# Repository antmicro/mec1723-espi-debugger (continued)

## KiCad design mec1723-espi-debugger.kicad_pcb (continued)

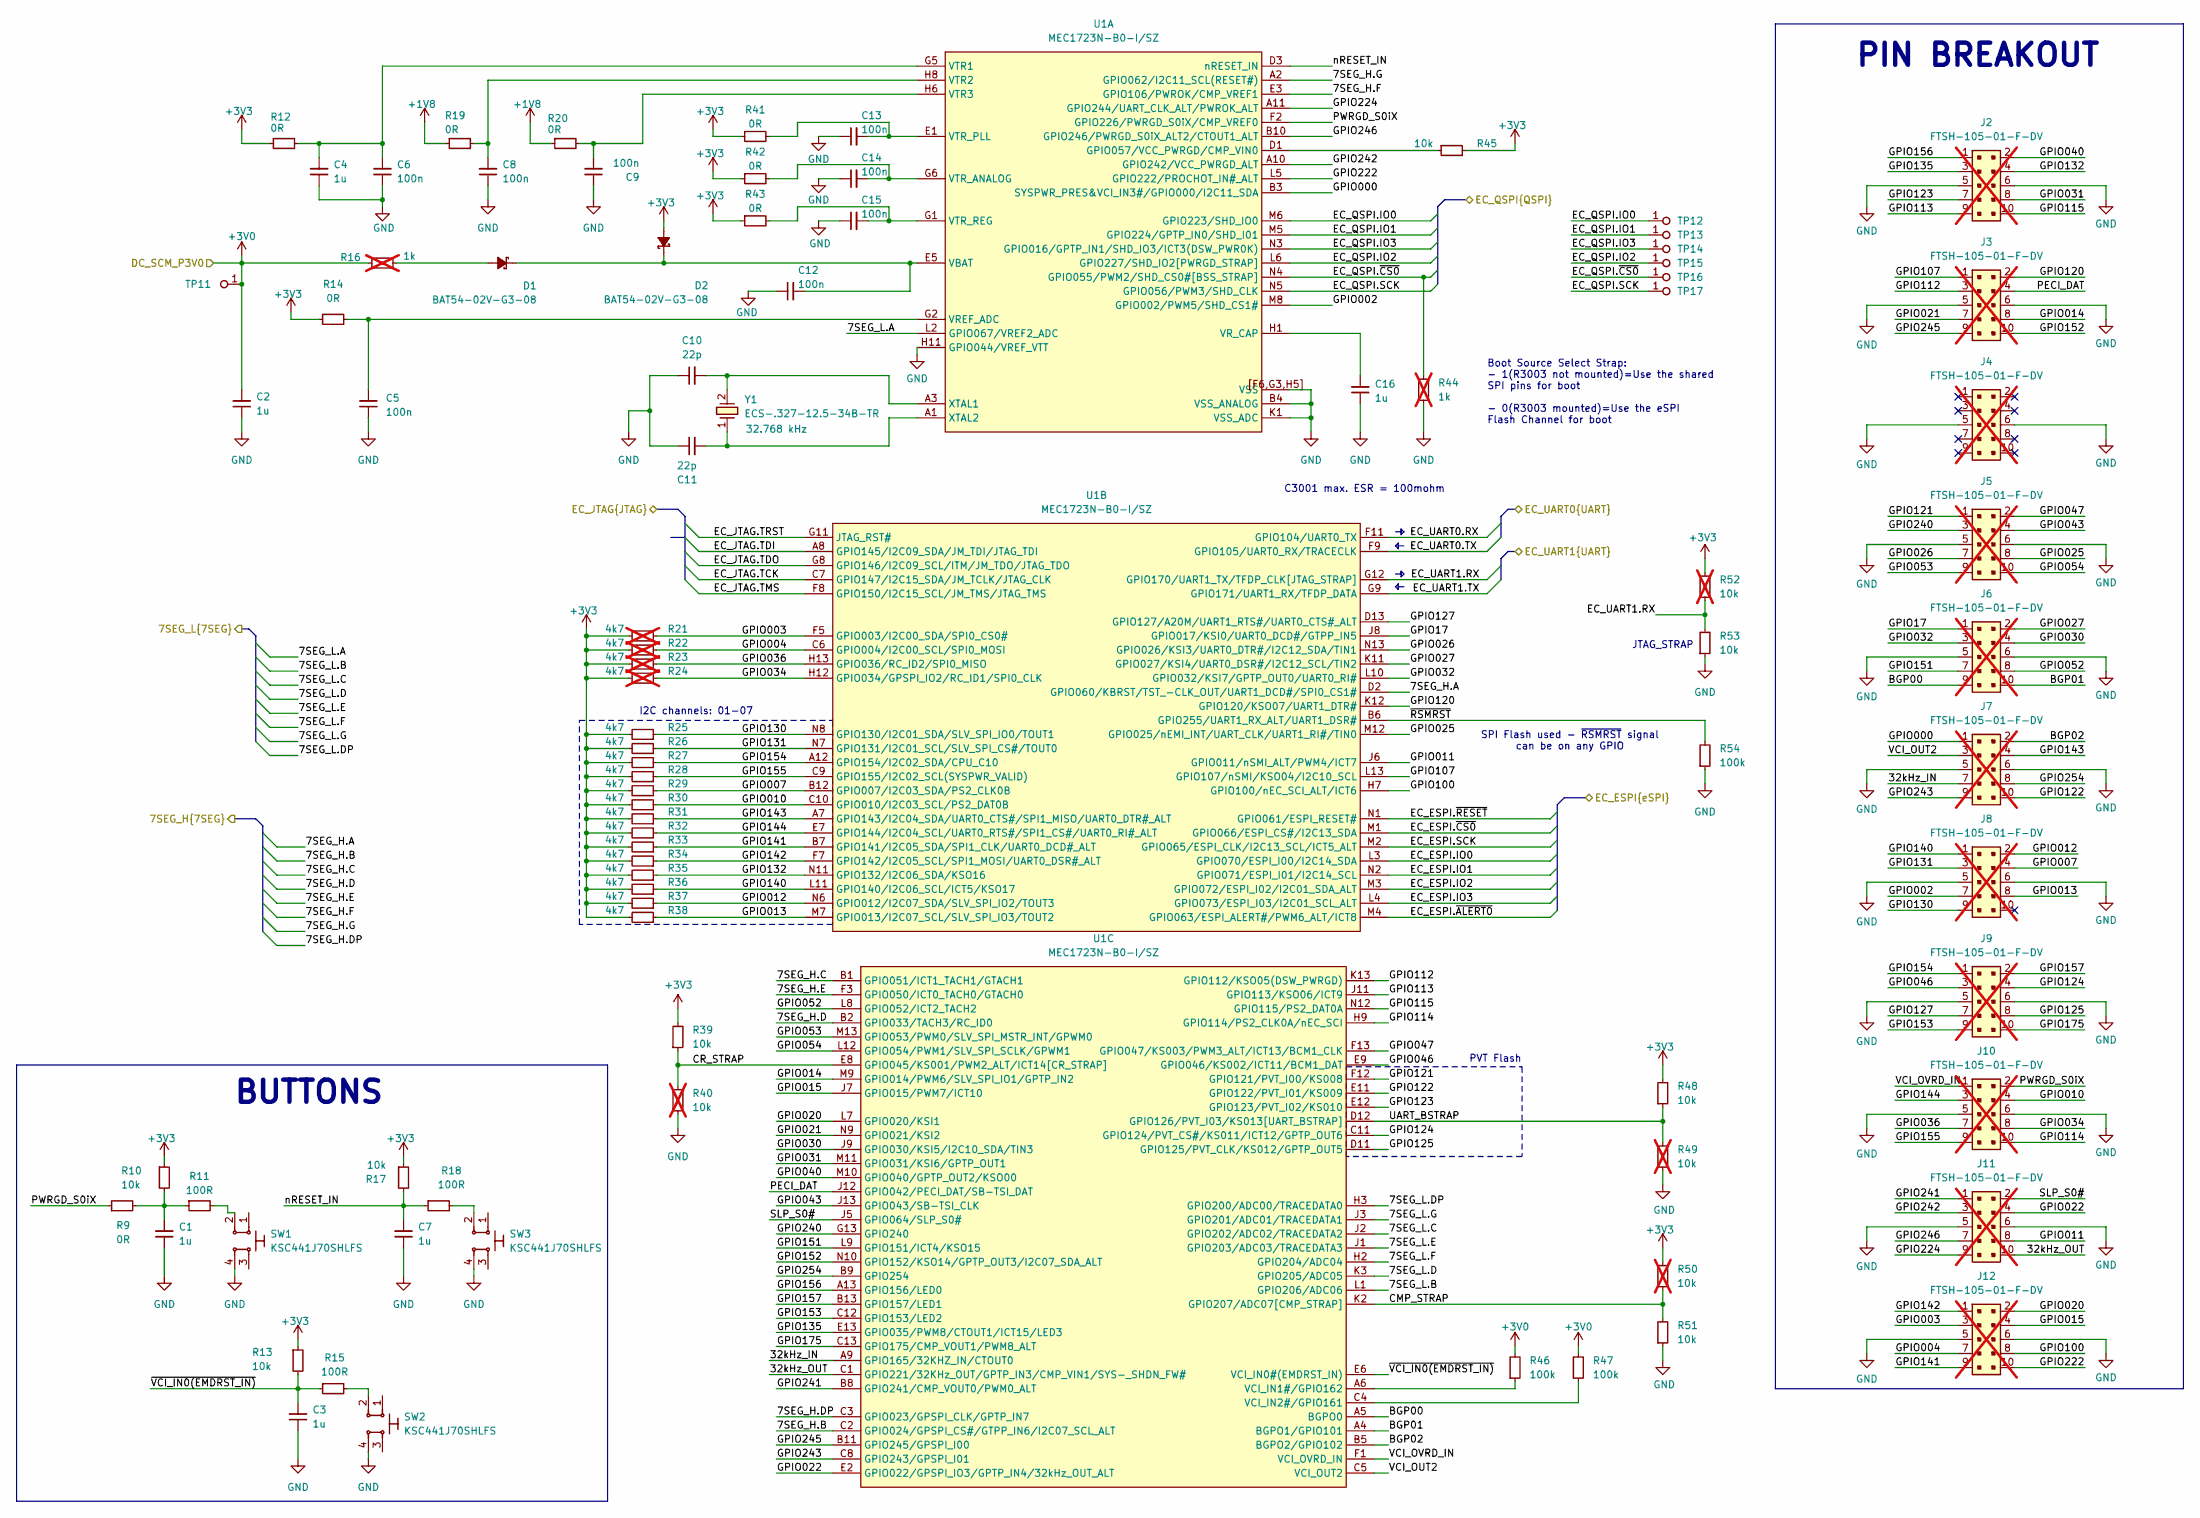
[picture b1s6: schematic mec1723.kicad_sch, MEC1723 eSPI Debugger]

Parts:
C1, C3, C7: C_1u_6.3V_X6S_0402; C_0402_1005Metric; Voltage 6.3V; MPN GRT155C80J105KE01D
C2, C4, C16: C_1u_0603; C_0603_1608Metric; MPN 0603YD105KAT2A
C5, C9, C12, C13, C14, C15: C_100n_0402; C_0402_1005Metric; Voltage 50V; MPN GRM155R61H104KE14D
C6, C8: C_100n_16V_X7R_0402; C_0402_1005Metric; Voltage 16V; MPN C0402C104J4RAC7411
C10, C11: C_22p_0402; C_0402_1005Metric; MPN CC0402JRNPO9BN220
D1, D2: BAT54-02V-G3-08; SOD-523; MPN BAT54-02V-G3-08
J2, J3, J4, J5, J6, J7, J8, J9, J10, J11, J12: PinHeader_2x5_P1.27mm_SMD; MPN FTSH-105-01-F-DV; not fitted
R9, R12, R14, R19, R20, R41, R42, R43: R_0R_0402; R_0402_1005Metric; MPN ERJ2GE0R00X
R10, R13, R17, R39, R45, R48, R51, R53: R_10k_0402; R_0402_1005Metric; Tolerance 1%; MPN CR0402-FX-1002GLF
R11, R15, R18: R_100R_0402; R_0402_1005Metric; Tolerance 1%; MPN CR0402-FX-1000GLF
R16, R44: R_1k_0402; R_0402_1005Metric; Tolerance 1%; MPN CR0402-FX-1001GLF; not fitted
R21, R22, R23, R24: R_4k7_0402; R_0402_1005Metric; Tolerance 1%; MPN CR0402-FX-4701GLF; not fitted
R25, R26, R27, R28, R29, R30, R31, R32, R33, R34, R35, R36, R37, R38: R_4k7_0402; R_0402_1005Metric; Tolerance 1%; MPN CR0402-FX-4701GLF
R40, R49, R50, R52: R_10k_0402; R_0402_1005Metric; Tolerance 1%; MPN CR0402-FX-1002GLF; not fitted
R46, R47, R54: R_100k_0402; R_0402_1005Metric; Tolerance 1%; MPN CR0402-FX-1003GLF
SW1, SW2, SW3: SW_KSC441J70SHLFS_SMD; MPN KSC441J70SHLFS
TP11, TP12, TP13, TP14, TP15, TP16, TP17: TP_1mm_SMD; TP_SMD_1mm
U1: MEC1723N-B0-I/SZ; BGA-169-144_9x9mm_Layout13x13_P0.7mm; MPN MEC1723N-B0-I/SZ
Y1: Resonator_32.768kHz_ECX-31B; Resonator_SMD_ECS_ECX-31B_3.2x1.5x0.9mm; MPN ECS-.327-12.5-34B-TR

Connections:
+1V8: R19.1, R20.1; also elsewhere on the board
+3V0: C2.2, R16.1, R46.2, R47.2, TP11.1 (1_1); also elsewhere on the board
+3V3: D2.2 (A), R10.1, R12.1, R13.1, R14.1, R17.1, R21.2, R22.2, R23.2, R24.2, R25.2, R26.2, R27.2, R28.2, R29.2, R30.2, R31.2, R32.2, R33.2, R34.2, R35.2, R36.2, R37.2, R38.2, R39.2, R41.1, R42.1, R43.1, R45.2, R48.2, R50.2, R52.2; also elsewhere on the board
/Connectors/EC_JTAG.TCK: U1.C7 (GPIO147/I2C15_SDA/JM_TCLK/JTAG_CLK); also elsewhere on the board
/Connectors/EC_JTAG.TDI: U1.A8 (GPIO145/I2C09_SDA/JM_TDI/JTAG_TDI); also elsewhere on the board
/Connectors/EC_JTAG.TDO: U1.G8 (GPIO146/I2C09_SCL/ITM/JM_TDO/JTAG_TDO); also elsewhere on the board
/Connectors/EC_JTAG.TMS: U1.F8 (GPIO150/I2C15_SCL/JM_TMS/JTAG_TMS); also elsewhere on the board
/Connectors/EC_JTAG.TRST: U1.G11 (JTAG_RST#); also elsewhere on the board
/Connectors/EC_UART0.RX: U1.F11 (GPIO104/UART0_TX); also elsewhere on the board
/Connectors/EC_UART0.TX: U1.F9 (GPIO105/UART0_RX/TRACECLK); also elsewhere on the board
/Connectors/EC_UART1.RX: R52.1, R53.2, U1.G12 (GPIO170/UART1_TX/TFDP_CLK[JTAG_STRAP]); also elsewhere on the board
/Connectors/EC_UART1.TX: U1.G9 (GPIO171/UART1_RX/TFDP_DATA); also elsewhere on the board
/DC-SCM Interposer connector/EC_ESPI.IO0: U1.L3 (GPIO070/ESPI_I00/I2C14_SDA); also elsewhere on the board
/DC-SCM Interposer connector/EC_ESPI.IO1: U1.N2 (GPIO071/ESPI_I01/I2C14_SCL); also elsewhere on the board
/DC-SCM Interposer connector/EC_ESPI.IO2: U1.M3 (GPIO072/ESPI_I02/I2C01_SDA_ALT); also elsewhere on the board
/DC-SCM Interposer connector/EC_ESPI.IO3: U1.L4 (GPIO073/ESPI_I03/I2C01_SCL_ALT); also elsewhere on the board
/DC-SCM Interposer connector/EC_ESPI.SCK: U1.M2 (GPIO065/ESPI_CLK/I2C13_SCL/ICT5_ALT); also elsewhere on the board
/DC-SCM Interposer connector/EC_ESPI.~ALERT0: U1.M4 (GPIO063/ESPI_ALERT#/PWM6_ALT/ICT8); also elsewhere on the board
/DC-SCM Interposer connector/EC_ESPI.~CS0: U1.M1 (GPIO066/ESPI_CS#/I2C13_SDA); also elsewhere on the board
/DC-SCM Interposer connector/EC_ESPI.~RESET: U1.N1 (GPIO061/ESPI_RESET#); also elsewhere on the board
/Flash/EC_QSPI.IO0: TP12.1 (1_1), U1.M6 (GPIO223/SHD_IO0); also elsewhere on the board
/Flash/EC_QSPI.IO1: TP13.1 (1_1), U1.M5 (GPIO224/GPTP_IN0/SHD_I01); also elsewhere on the board
/Flash/EC_QSPI.IO2: TP15.1 (1_1), U1.L6 (GPIO227/SHD_IO2[PWRGD_STRAP]); also elsewhere on the board
/Flash/EC_QSPI.IO3: TP14.1 (1_1), U1.N3 (GPIO016/GPTP_IN1/SHD_IO3/ICT3(DSW_PWR0K)); also elsewhere on the board
/Flash/EC_QSPI.SCK: TP17.1 (1_1), U1.N5 (GPIO056/PWM3/SHD_CLK); also elsewhere on the board
/Flash/EC_QSPI.~CS0: R44.2, TP16.1 (1_1), U1.N4 (GPIO055/PWM2/SHD_CS0#[BSS_STRAP]); also elsewhere on the board
/MEC1723/7SEG_H.A: U1.D2 (GPIO060/KBRST/TST_-CLK_OUT/UART1_DCD#/S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); also elsewhere on the board
/MEC1723/7SEG_H.B: U1.C2 (GPIO024/GPSPI_CS#/GTPP_IN6/I2C07_SCL_ALT); also elsewhere on the board
/MEC1723/7SEG_H.C: U1.B1 (GPIO051/ICT1_TACH1/GTACH1); also elsewhere on the board
/MEC1723/7SEG_H.D: U1.B2 (GPIO033/TACH3/RC_ID0); also elsewhere on the board
/MEC1723/7SEG_H.DP: U1.C3 (GPIO023/GPSPI_CLK/GPTP_IN7); also elsewhere on the board
/MEC1723/7SEG_H.E: U1.F3 (GPIO050/ICT0_TACH0/GTACH0); also elsewhere on the board
/MEC1723/7SEG_H.F: U1.E3 (GPIO106/PWROK/CMP_VREF1); also elsewhere on the board
/MEC1723/7SEG_H.G: U1.A2 (GPIO062/I2C11_SCL(RESET#)); also elsewhere on the board
/MEC1723/7SEG_L.A: U1.L2 (GPIO067/VREF2_ADC); also elsewhere on the board
/MEC1723/7SEG_L.B: U1.L1 (GPIO206/ADC06); also elsewhere on the board
/MEC1723/7SEG_L.C: U1.J2 (GPIO202/ADC02/TRACEDATA2); also elsewhere on the board
/MEC1723/7SEG_L.D: U1.K3 (GPIO205/ADC05); also elsewhere on the board
/MEC1723/7SEG_L.DP: U1.H3 (GPIO200/ADC00/TRACEDATA0); also elsewhere on the board
/MEC1723/7SEG_L.E: U1.J1 (GPIO203/ADC03/TRACEDATA3); also elsewhere on the board
/MEC1723/7SEG_L.F: U1.H2 (GPIO204/ADC04); also elsewhere on the board
/MEC1723/7SEG_L.G: U1.J3 (GPIO201/ADC01/TRACEDATA1); also elsewhere on the board
/MEC1723/32kHz_IN: J7.7, U1.A9 (GPIO165/32KHZ_IN/CTOUT0)
/MEC1723/32kHz_OUT: J11.10, U1.C1 (GPIO221/32KHz_OUT/GPTP_IN3/CMP_VIN1/SYS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)
/MEC1723/BGP00: J6.9, U1.A5 (BGPO0)
/MEC1723/BGP01: J6.10, U1.A4 (BGPO1/GPIO101)
/MEC1723/BGP02: J7.2, U1.B5 (BGPO2/GPIO102)
/MEC1723/CMP_STRAP: R50.1, R51.2, U1.K2 (GPIO207/ADC07[CMP_STRAP])
/MEC1723/CR_STRAP: R39.1, R40.2, U1.E8 (GPIO045/KS001/PWM2_ALT/ICT14[CR_STRAP])
/MEC1723/GPIO000: J7.1, U1.B3 (SYSPWR_PRES&VCI_IN3#/GPIO000/I2C11_SDA)
/MEC1723/GPIO002: J8.7, U1.M8 (GPIO002/PWM5/SHD_CS1#)
/MEC1723/GPIO003: J12.3, R21.1, U1.F5 (GPIO003/I2C00_SDA/SPI0_CS0#)
/MEC1723/GPIO004: J12.7, R22.1, U1.C6 (GPIO004/I2C00_SCL/SPI0_MOSI)
/MEC1723/GPIO007: J8.4, R29.1, U1.B12 (GPIO007/I2C03_SDA/PS2_CLK0B)
/MEC1723/GPIO010: J10.4, R30.1, U1.C10 (GPIO010/I2C03_SCL/PS2_DAT0B)
/MEC1723/GPIO011: J11.8, U1.J6 (GPIO011/nSMI_ALT/PWM4/ICT7)
/MEC1723/GPIO012: J8.2, R37.1, U1.N6 (GPIO012/I2C07_SDA/SLV_SPI_IO2/TOUT3)
/MEC1723/GPIO013: J8.8, R38.1, U1.M7 (GPIO013/I2C07_SCL/SLV_SPI_IO3/TOUT2)
/MEC1723/GPIO014: J3.8, U1.M9 (GPIO014/PWM6/SLV_SPI_IO1/GPTP_IN2)
/MEC1723/GPIO015: J12.4, U1.J7 (GPIO015/PWM7/ICT10)
/MEC1723/GPIO17: J6.1, U1.J8 (GPIO017/KSI0/UART0_DCD#/GTPP_IN5)
/MEC1723/GPIO020: J12.2, U1.L7 (GPIO020/KSI1)
/MEC1723/GPIO021: J3.7, U1.N9 (GPIO021/KSI2)
/MEC1723/GPIO022: J11.4, U1.E2 (GPIO022/GPSPI_IO3/GPTP_IN4/32kHz_OUT_ALT)
/MEC1723/GPIO025: J5.8, U1.M12 (GPIO025/nEMI_INT/UART_CLK/UART1_RI#/TIN0)
/MEC1723/GPIO026: J5.7, U1.N13 (GPIO026/KSI3/UART0_DTR#/I2C12_SDA/TIN1)
/MEC1723/GPIO027: J6.2, U1.K11 (GPIO027/KSI4/UART0_DSR#/I2C12_SCL/TIN2)
/MEC1723/GPIO030: J6.4, U1.J9 (GPIO030/KSI5/I2C10_SDA/TIN3)
/MEC1723/GPIO031: J2.8, U1.M11 (GPIO031/KSI6/GPTP_OUT1)
/MEC1723/GPIO032: J6.3, U1.L10 (GPIO032/KSI7/GPTP_OUT0/UART0_RI#)
/MEC1723/GPIO034: J10.8, R24.1, U1.H12 (GPIO034/GPSPI_IO2/RC_ID1/SPI0_CLK)
/MEC1723/GPIO036: J10.7, R23.1, U1.H13 (GPIO036/RC_ID2/SPI0_MISO)
/MEC1723/GPIO040: J2.2, U1.M10 (GPIO040/GPTP_OUT2/KSO00)
/MEC1723/GPIO043: J5.4, U1.J13 (GPIO043/SB-TSI_CLK)
/MEC1723/GPIO046: J9.3, U1.E9 (GPIO046/KS002/ICT11/BCM1_DAT)
/MEC1723/GPIO047: J5.2, U1.F13 (GPIO047/KS003/PWM3_ALT/ICT13/BCM1_CLK)
/MEC1723/GPIO052: J6.8, U1.L8 (GPIO052/ICT2_TACH2)
/MEC1723/GPIO053: J5.9, U1.M13 (GPIO053/PWM0/SLV_SPI_MSTR_INT/GPWM0)
/MEC1723/GPIO054: J5.10, U1.L12 (GPIO054/PWM1/SLV_SPI_SCLK/GPWM1)
/MEC1723/GPIO100: J12.8, U1.H7 (GPIO100/nEC_SCI_ALT/ICT6)
/MEC1723/GPIO107: J3.1, U1.L13 (GPIO107/nSMI/KSO04/I2C10_SCL)
/MEC1723/GPIO112: J3.3, U1.K13 (GPIO112/KSO05(DSW_PWRGD))
/MEC1723/GPIO113: J2.9, U1.J11 (GPIO113/KSO06/ICT9)
/MEC1723/GPIO114: J10.10, U1.H9 (GPIO114/PS2_CLK0A/nEC_SCI)
/MEC1723/GPIO115: J2.10, U1.N12 (GPIO115/PS2_DAT0A)
/MEC1723/GPIO120: J3.2, U1.K12 (GPIO120/KSO07/UART1_DTR#)
/MEC1723/GPIO121: J5.1, U1.F12 (GPIO121/PVT_I00/KS008)
/MEC1723/GPIO122: J7.10, U1.E11 (GPIO122/PVT_I01/KS009)
/MEC1723/GPIO123: J2.7, U1.E12 (GPIO123/PVT_I02/KS010)
/MEC1723/GPIO124: J9.4, U1.C11 (GPIO124/PVT_CS#/KS011/ICT12/GPTP_OUT6)
/MEC1723/GPIO125: J9.8, U1.D11 (GPIO125/PVT_CLK/KS012/GPTP_OUT5)
/MEC1723/GPIO127: J9.7, U1.D13 (GPIO127/A20M/UART1_RTS#/UART0_CTS#_ALT)
/MEC1723/GPIO130: J8.9, R25.1, U1.N8 (GPIO130/I2C01_SDA/SLV_SPI_IO0/TOUT1)
/MEC1723/GPIO131: J8.3, R26.1, U1.N7 (GPIO131/I2C01_SCL/SLV_SPI_CS#/TOUT0)
/MEC1723/GPIO132: J2.4, R35.1, U1.N11 (GPIO132/I2C06_SDA/KSO16)
/MEC1723/GPIO135: J2.3, U1.E13 (GPIO035/PWM8/CTOUT1/ICT15/LED3)
/MEC1723/GPIO140: J8.1, R36.1, U1.L11 (GPIO140/I2C06_SCL/ICT5/KSO17)
/MEC1723/GPIO141: J12.9, R33.1, U1.B7 (GPIO141/I2C05_SDA/SPI1_CLK/UART0_DCD#_A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)
/MEC1723/GPIO142: J12.1, R34.1, U1.F7 (GPIO142/I2C05_SCL/SPI1_MOSI/UART0_DSR#_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)
/MEC1723/GPIO143: J7.4, R31.1, U1.A7 (GPIO143/I2C04_SDA/UART0_CTS#/SPI1_MISO/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)
/MEC1723/GPIO144: J10.3, R32.1, U1.E7 (GPIO144/I2C04_SCL/UART0_RTS#/SPI1_CS#/U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)
/MEC1723/GPIO151: J6.7, U1.L9 (GPIO151/ICT4/KSO15)
/MEC1723/GPIO152: J3.10, U1.N10 (GPIO152/KSO14/GPTP_OUT3/I2C07_SDA_ALT)
/MEC1723/GPIO153: J9.9, U1.C12 (GPIO153/LED2)
/MEC1723/GPIO154: J9.1, R27.1, U1.A12 (GPIO154/I2C02_SDA/CPU_C10)
/MEC1723/GPIO155: J10.9, R28.1, U1.C9 (GPIO155/I2C02_SCL(SYSPWR_VALID))
/MEC1723/GPIO156: J2.1, U1.A13 (GPIO156/LED0)
/MEC1723/GPIO157: J9.2, U1.B13 (GPIO157/LED1)
/MEC1723/GPIO175: J9.10, U1.C13 (GPIO175/CMP_VOUT1/PWM8_ALT)
/MEC1723/GPIO222: J12.10, U1.L5 (GPIO222/PROCHOT_IN#_ALT)
/MEC1723/GPIO224: J11.9, U1.A11 (GPIO244/UART_CLK_ALT/PWROK_ALT)
/MEC1723/GPIO240: J5.3, U1.G13 (GPIO240)
/MEC1723/GPIO241: J11.1, U1.B8 (GPIO241/CMP_VOUT0/PWM0_ALT)
/MEC1723/GPIO242: J11.3, U1.A10 (GPIO242/VCC_PWRGD_ALT)
/MEC1723/GPIO243: J7.9, U1.C8 (GPIO243/GPSPI_I01)
/MEC1723/GPIO245: J3.9, U1.B11 (GPIO245/GPSPI_I00)
/MEC1723/GPIO246: J11.7, U1.B10 (GPIO246/PWRGD_S0iX_ALT2/CTOUT1_ALT)
/MEC1723/GPIO254: J7.8, U1.B9 (GPIO254)
/MEC1723/PECI_DAT: J3.4, U1.J12 (GPIO042/PECI_DAT/SB-TSI_DAT)
/MEC1723/PWRGD_S0iX: J10.2, R9.1, U1.F2 (GPIO226/PWRGD_S0iX/CMP_VREF0)
/MEC1723/SLP_S0#: J11.2, U1.J5 (GPIO064/SLP_S0#)
/MEC1723/UART_BSTRAP: R48.1, R49.2, U1.D12 (GPIO126/PVT_I03/KS013[UART_BSTRAP])
/MEC1723/VCI_OUT2: J7.3, U1.C5 (VCI_OUT2)
/MEC1723/VCI_OVRD_IN: J10.1, U1.F1 (VCI_OVRD_IN)
/MEC1723/nRESET_IN: C7.2, R17.2, R18.1, U1.D3 (nRESET_IN)
/MEC1723/~RSMRST: R54.2, U1.B6 (GPIO255/UART1_RX_ALT/UART1_DSR#)
/MEC1723/~VCI_IN0(EMDRST_IN): C3.2, R13.2, R15.1, U1.E6 (VCI_IN0#(EMDRST_IN))
GND: C1.1, C2.1, C3.1, C4.1, C5.1, C6.1, C7.1, C8.1, C9.1, C10.1, C11.1, C12.1, C13.1, C14.1, C15.1, C16.1, J2.5, J2.6, J3.5, J3.6, J4.5, J4.6, J5.5, J5.6, J6.5, J6.6, J7.5, J7.6, J8.5, J8.6, J9.5, J9.6, J10.5, J10.6, J11.5, J11.6, J12.5, J12.6, R40.1, R44.1, R49.1, R51.1, R53.1, R54.1, SW1.4, SW2.4, SW3.4, U1.B4 (VSS_ANALOG), U1.F6 (VSS), U1.G3 (VSS), U1.H5 (VSS), U1.H11 (GPIO044/VREF_VTT), U1.K1 (VSS_ADC), U1.[F6,G3,H5] (VSS); also elsewhere on the board
unnamed: C1.2, R9.2, R10.2, R11.1
unnamed: D1.2 (A), R16.2
unnamed: C12.2, D1.1 (C), D2.1 (C), U1.E5 (VBAT)
unnamed: R11.2, SW1.2
unnamed: R15.2, SW2.2
unnamed: R18.2, SW3.2
unnamed: R45.1, U1.D1 (GPIO057/VCC_PWRGD/CMP_VIN0)
unnamed: C5.2, R14.2, U1.G2 (VREF_ADC)
unnamed: C16.2, U1.H1 (VR_CAP)
unnamed: C4.2, C6.2, R12.2, U1.G5 (VTR1)
unnamed: C8.2, R19.2, U1.H8 (VTR2)
unnamed: C9.2, R20.2, U1.H6 (VTR3)
unnamed: C14.2, R42.2, U1.G6 (VTR_ANALOG)
unnamed: C13.2, R41.2, U1.E1 (VTR_PLL)
unnamed: C15.2, R43.2, U1.G1 (VTR_REG)
unnamed: C10.2, U1.A3 (XTAL1), Y1.2
unnamed: C11.2, U1.A1 (XTAL2), Y1.1
unnamed: R46.1, U1.A6 (VCI_IN1#/GPIO162)
unnamed: R47.1, U1.C4 (VCI_IN2#/GPIO161)

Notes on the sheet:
Boot Source Select Strap: - 1(R3003 not mounted)=Use the shared SPI pins for boot - 0(R3003 mounted)=Use the eSPI Flash Channel for boot
SPI Flash used - ~{RSMRST} signal can be on any GPIO
I2C channels: 01-07
C3001 max. ESR = 100mohm
PIN BREAKOUT
PVT Flash
JTAG_STRAP
BUTTONS

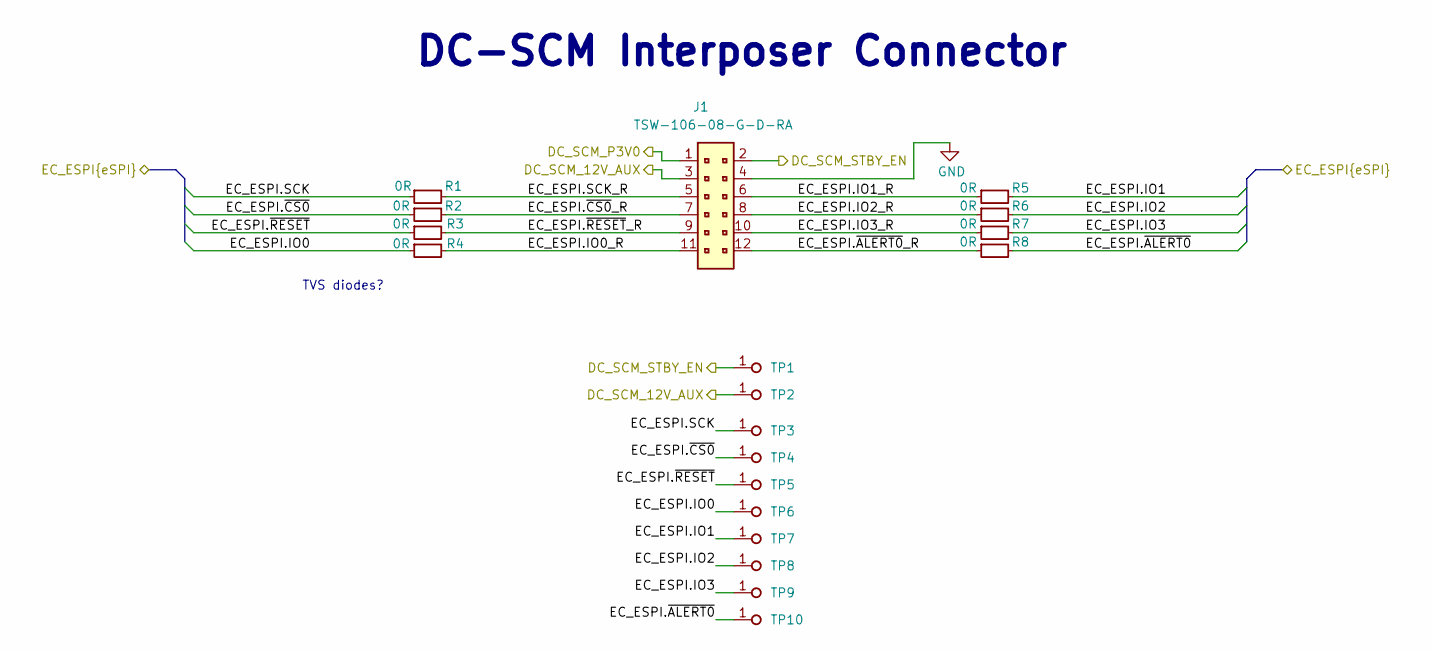
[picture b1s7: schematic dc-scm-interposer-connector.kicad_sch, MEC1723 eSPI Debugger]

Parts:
J1: PinHeader_2x6_P2.54mm_Drill1.1mm_Horizontal; PinHeader_2x6_P2.54mm_Drill1.1mm_Horizontal_ALT; MPN TSW-106-08-G-D-RA
R1, R2, R3, R4, R5, R6, R7, R8: R_0R_0402; R_0402_1005Metric; MPN ERJ2GE0R00X
TP1, TP2: TP_1mm_SMD; TP_SMD_1mm
TP3, TP4, TP5, TP6, TP7, TP8, TP9, TP10: TP_0.75mm_SMD; TP_SMD_0.75mm

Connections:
+3V0: J1.1; also elsewhere on the board
/DC-SCM Interposer connector/DC_SCM_12V_AUX: J1.3, TP2.1 (1_1); also elsewhere on the board
/DC-SCM Interposer connector/DC_SCM_STBY_EN: J1.2, TP1.1 (1_1); also elsewhere on the board
/DC-SCM Interposer connector/EC_ESPI.IO0: R4.1, TP6.1 (1_1); also elsewhere on the board
/DC-SCM Interposer connector/EC_ESPI.IO0_R: J1.11, R4.2
/DC-SCM Interposer connector/EC_ESPI.IO1: R5.2, TP7.1 (1_1); also elsewhere on the board
/DC-SCM Interposer connector/EC_ESPI.IO1_R: J1.6, R5.1
/DC-SCM Interposer connector/EC_ESPI.IO2: R6.2, TP8.1 (1_1); also elsewhere on the board
/DC-SCM Interposer connector/EC_ESPI.IO2_R: J1.8, R6.1
/DC-SCM Interposer connector/EC_ESPI.IO3: R7.2, TP9.1 (1_1); also elsewhere on the board
/DC-SCM Interposer connector/EC_ESPI.IO3_R: J1.10, R7.1
/DC-SCM Interposer connector/EC_ESPI.SCK: R1.1, TP3.1 (1_1); also elsewhere on the board
/DC-SCM Interposer connector/EC_ESPI.SCK_R: J1.5, R1.2
/DC-SCM Interposer connector/EC_ESPI.~ALERT0: R8.2, TP10.1 (1_1); also elsewhere on the board
/DC-SCM Interposer connector/EC_ESPI.~ALERT0_R: J1.12, R8.1
/DC-SCM Interposer connector/EC_ESPI.~CS0: R2.1, TP4.1 (1_1); also elsewhere on the board
/DC-SCM Interposer connector/EC_ESPI.~CS0_R: J1.7, R2.2
/DC-SCM Interposer connector/EC_ESPI.~RESET: R3.1, TP5.1 (1_1); also elsewhere on the board
/DC-SCM Interposer connector/EC_ESPI.~RESET_R: J1.9, R3.2
GND: J1.4; also elsewhere on the board

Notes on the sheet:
DC-SCM Interposer Connector
TVS diodes?

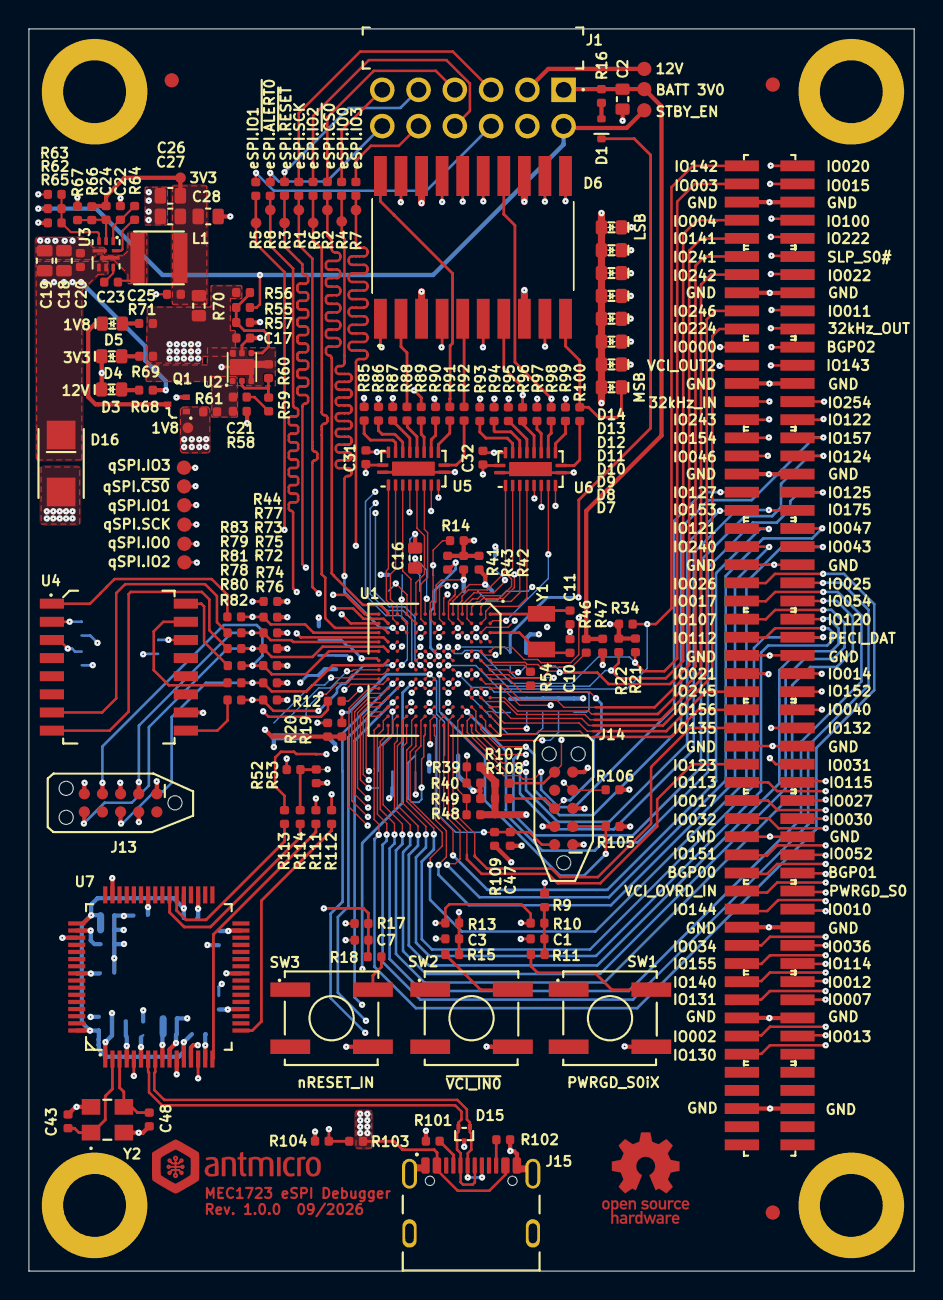
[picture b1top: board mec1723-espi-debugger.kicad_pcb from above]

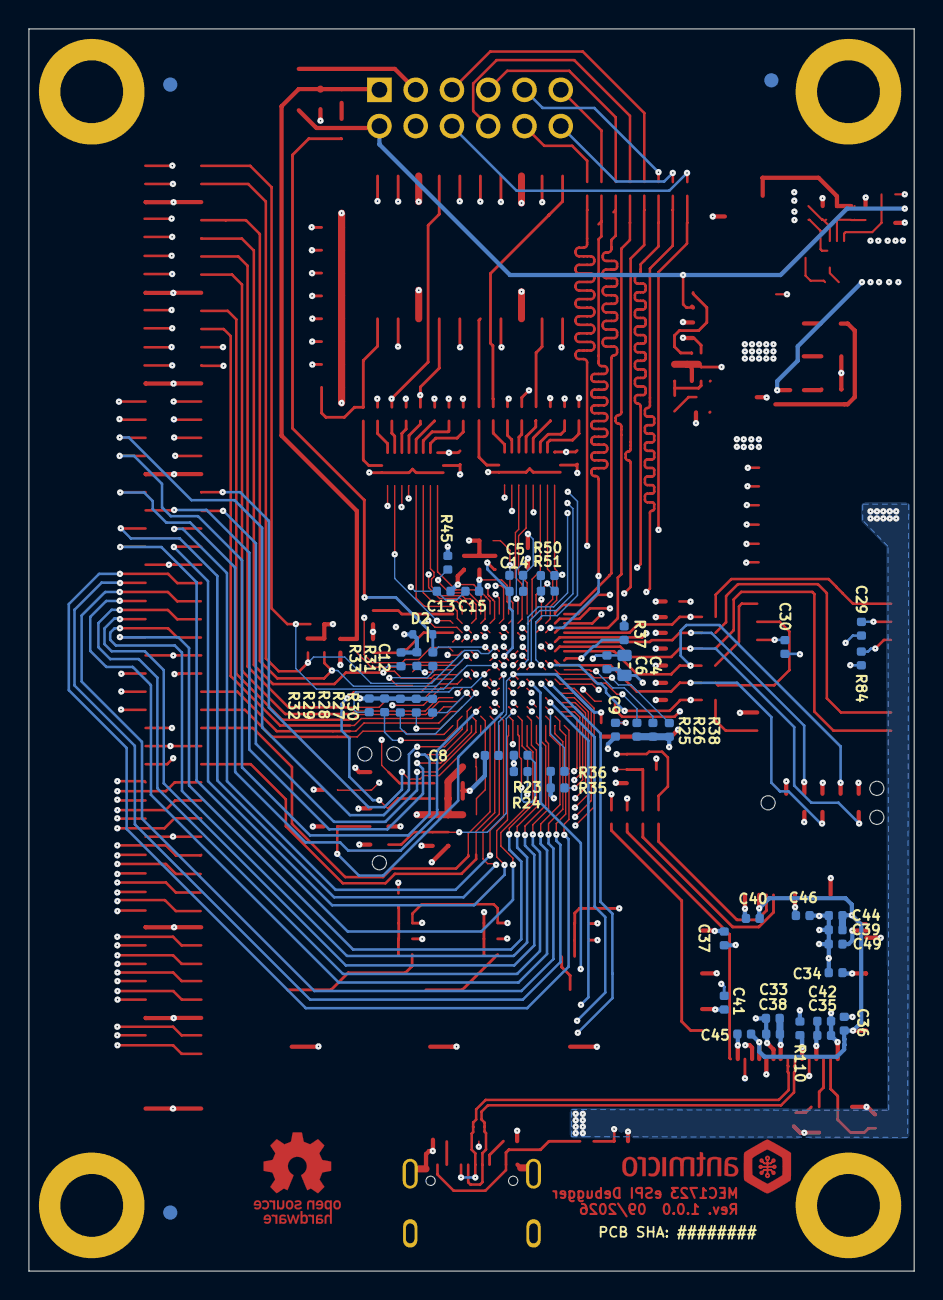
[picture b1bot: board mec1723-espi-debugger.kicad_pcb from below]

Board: 8 copper layers, 62.0 x 87.0 mm, 239 parts (53 on the bottom side), 225 nets.
